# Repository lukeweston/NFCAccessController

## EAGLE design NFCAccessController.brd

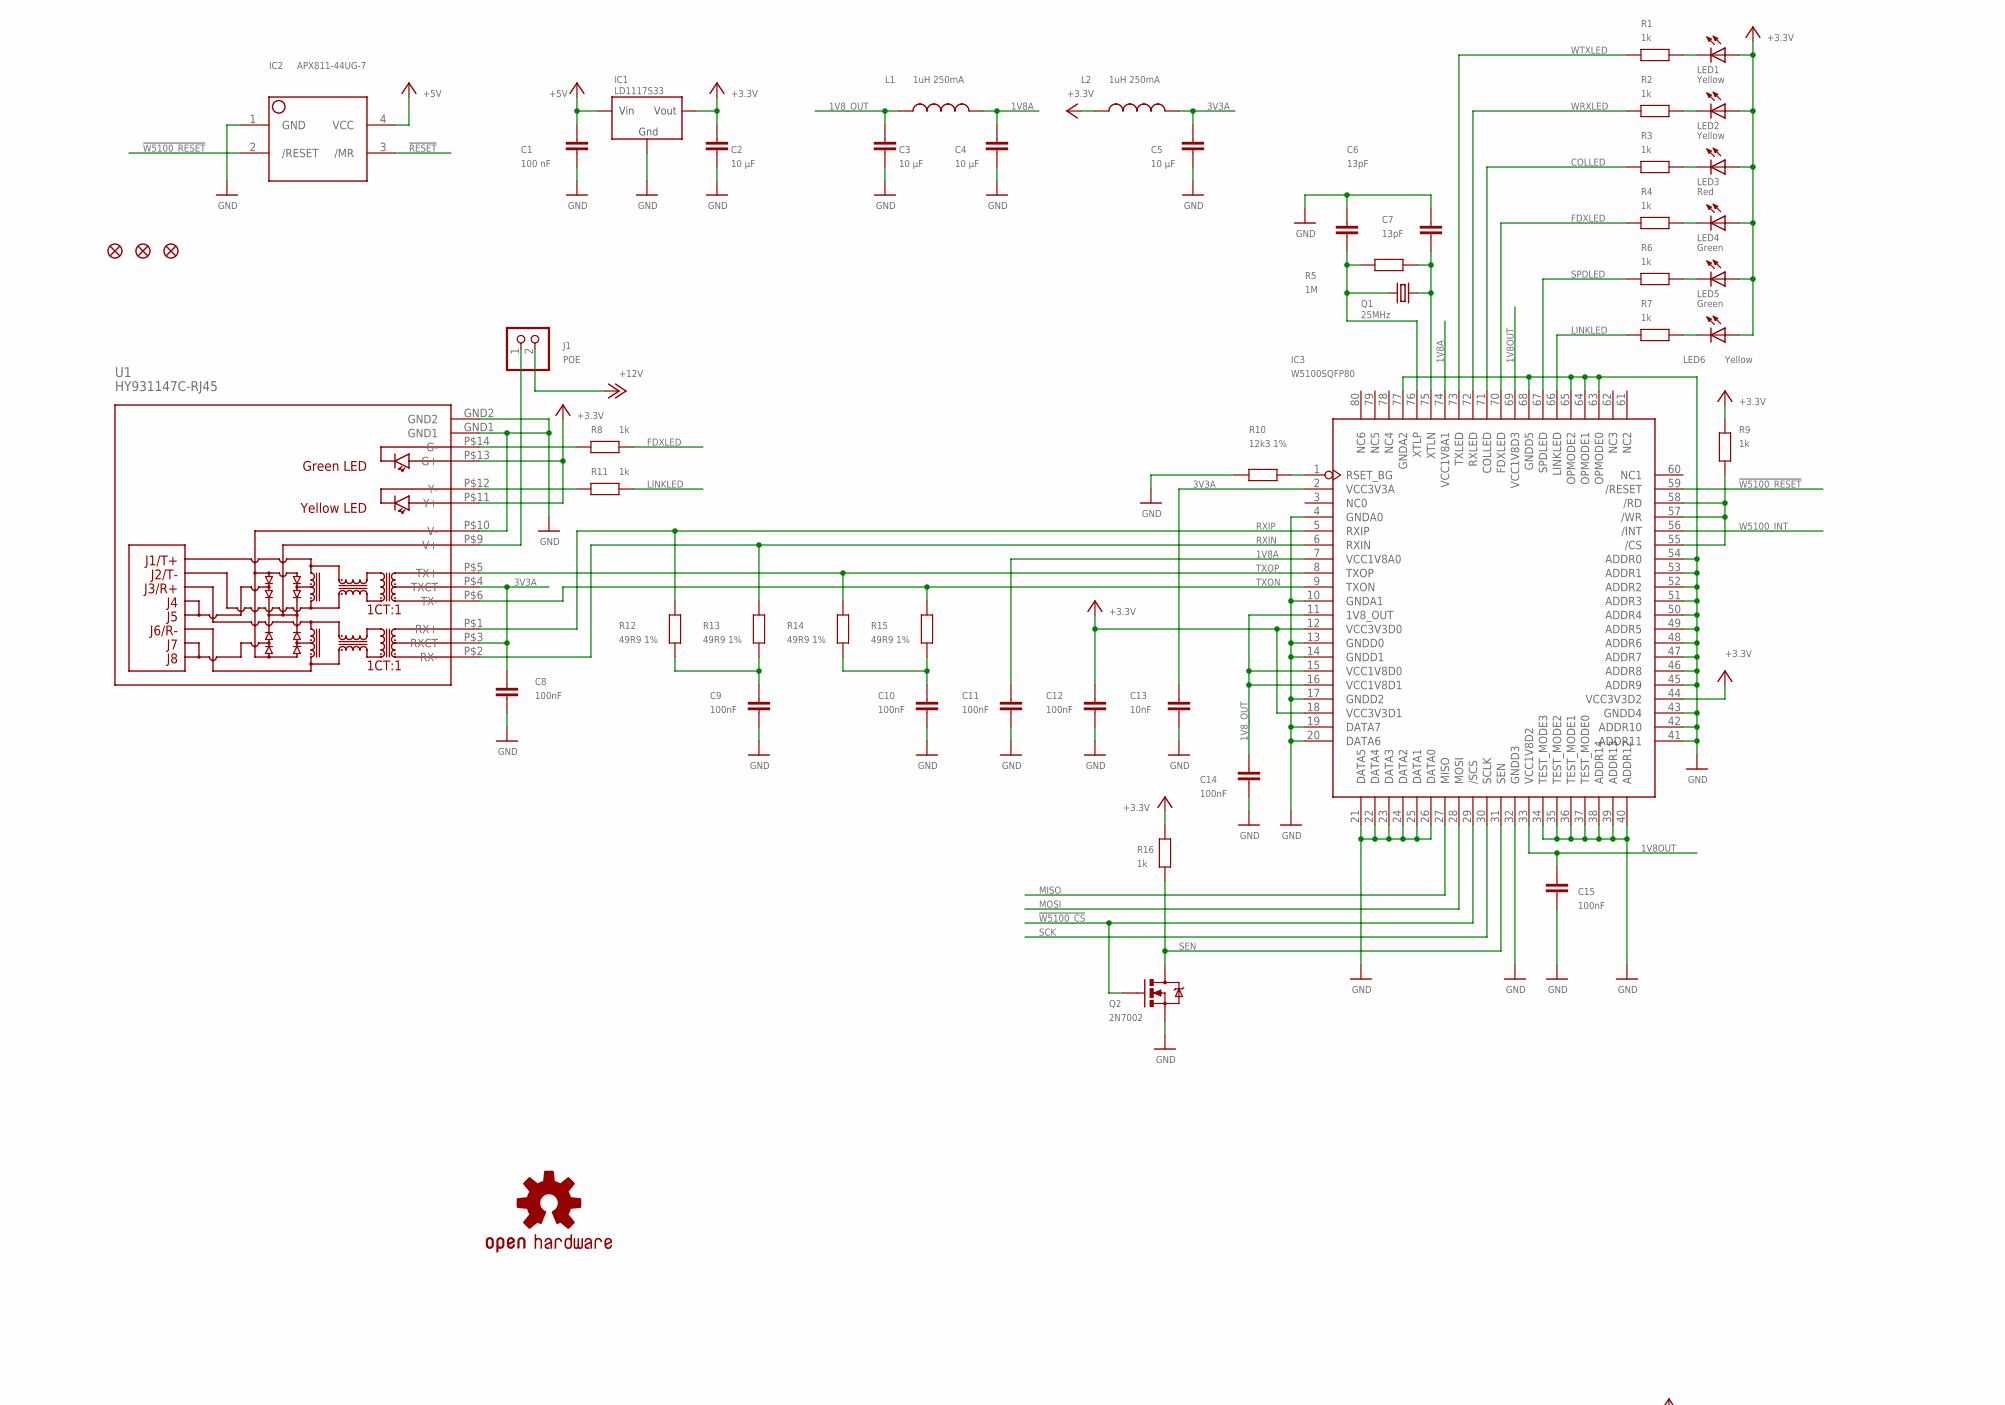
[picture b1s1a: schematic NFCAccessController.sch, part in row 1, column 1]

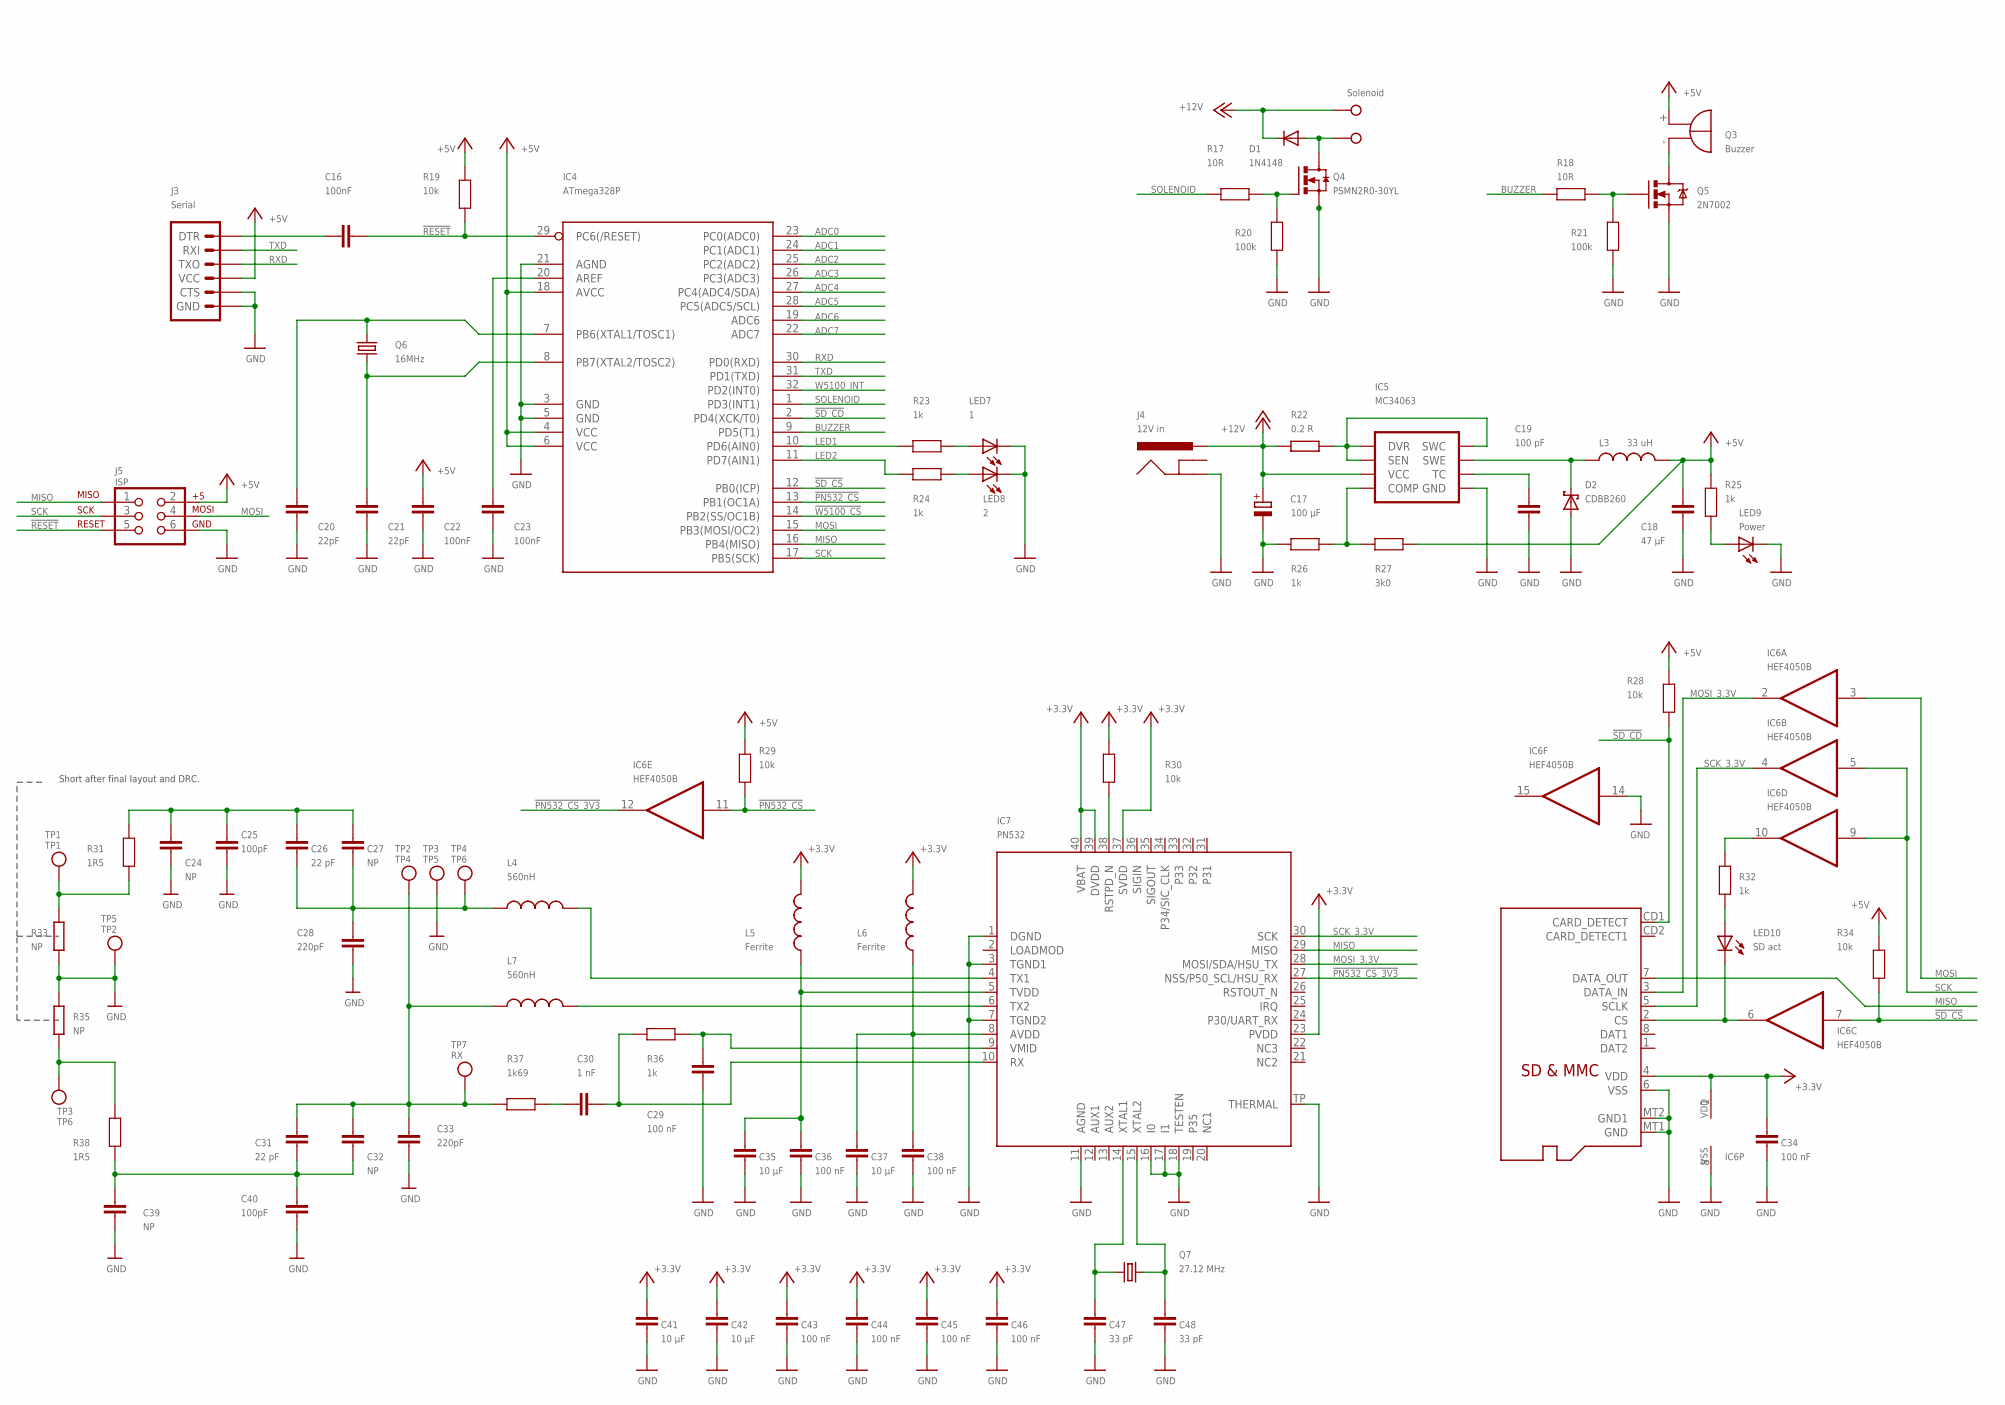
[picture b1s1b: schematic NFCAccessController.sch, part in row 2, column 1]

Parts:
C1, C29, C34, C36, C38, C43, C44, C45, C46: 100 nF; 0603
C2, C3, C4, C5, C35, C37, C41, C42: 10 µF; 0805
C6, C7: 13pF; 0603
C8, C9, C10, C11, C12, C14, C15, C16, C22, C23: 100nF; 0603
C13: 10nF; 0603
C17: 100 µF; E2,5-6
C18: 47 µF; C1210
C19: 100 pF; 0603
C20, C21: 22pF; 0603
C24, C27, C32, C39: NP; 0603
C25, C40: 100pF; 0603
C26, C31: 22 pF; 0603
C28, C33: 220pF; 0603
C30: 1 nF; 0603
C47, C48: 33 pF; 0603
D1: 1N4148; SOD-323
D2: CDBB260; SMB
FID1, FID2, FID3: FIDUCIAL1X2.5; FIDUCIAL-1X2.5
IC1: LD1117S33; SOT223; MPN REG1117
IC2: APX811-44UG-7; SOT143-R
IC3: W5100SQFP80; SQFP80
IC4: ATmega328P; TQFP32-08
IC5: MC34063; SO08
IC6: HEF4050B; SO16
IC7: PN532; HVQFN40-6X6
J1: POE; 1X02
J2: Solenoid; W237-132
J3: Serial; 1X06_LONGPADS
J4: 12V in; POWER_JACK_SLOT
J5: ISP; 2X3-NS
J6: MicroSD Card; ADAFRUIT_MICROSD
L1, L2: 1uH 250mA; L2012C
L3: 33 uH; CR75
L4, L7: 560nH; 0603
L5, L6: Ferrite; 0805-LARGE
LED1, LED2, LED6: Yellow; LED-0603
LED3: Red; LED-0603
LED4, LED5: Green; LED-0603
LED7: 1; LED-0603
LED8: 2; LED-0603
LED9: Power; LED-0603
LED10: SD act; LED-0603
Q1: 25MHz; HC49U-V
Q2, Q5: 2N7002; SOT23-3
Q3: Buzzer; F/TMB
Q4: PSMN2R0-30YL; SOT669
Q6: 16MHz; HC49U-V
Q7: 27.12 MHz; CRYSTAL-SMD-5X3
R1, R2, R3, R4, R6, R7, R8, R9, R11, R16, R23, R24, R25, R26, R32, R36: 1k; 0603
R5: 1M; 0603
R10: 12k3 1%; 0603
R12, R13, R14, R15: 49R9 1%; 0603
R17, R18: 10R; 0603
R19, R28, R29, R30, R34: 10k; 0603
R20, R21: 100k; 0603
R22: 0.2 R; R1210
R27: 3k0; 0603
R31, R38: 1R5; 0603
R33, R35: NP; R0201
R37: 1k69; 0603
S$1: OSHW-LOGOS; OSHW-LOGO-S
TP1: TP1; TESTPOINT_PAD_2MM
TP2: TP4; TESTPOINT_PAD_2MM
TP3: TP5; TESTPOINT_PAD_2MM
TP4: TP6; TESTPOINT_PAD_2MM
TP5: TP2; TESTPOINT_PAD_2MM
TP6: TP3; TESTPOINT_PAD_2MM
TP7: RX; TESTPOINT_PAD_2MM
U1: HY931147C-RJ45; HY931147C

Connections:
1V8A: C4.1, C11.1, IC3.7 (VCC1V8A0), IC3.74 (VCC1V8A1), L1.2
1V8OUT: C15.1, IC3.33 (VCC1V8D2), IC3.69 (VCC1V8D3)
1V8_OUT: C3.1, C14.1, IC3.11 (1V8_OUT), IC3.15 (VCC1V8D0), IC3.16 (VCC1V8D1), L1.1
3V3A: C5.1, C8.1, C13.1, IC3.2 (VCC3V3A), L2.2, U1.P$3 (RXCT), U1.P$4 (TXCT)
!PN532_CS: IC4.13 (PB1(OC1A)), IC6.11 (I), R29.2
!PN532_CS_3V3: IC6.12 (O), IC7.27 (NSS/P50_SCL/HSU_RX)
!RESET: C16.2, IC2.3 (/MR), IC4.29 (PC6(/RESET)), J5.5, R19.1
!SD_CD: IC4.2 (PD4(XCK/T0)), J6.CD1 (CARD_DETECT), R28.1
!SD_CS: IC4.12 (PB0(ICP)), IC6.7 (I), R34.1
!W5100_CS: IC3.29 (/SCS), IC4.14 (PB2(SS/OC1B)), Q2.1 (G)
!W5100_RESET: IC2.2 (/RESET), IC3.59 (/RESET)
+3V3: C2.1, C12.1, C34.1, C41.1, C42.1, C43.1, C44.1, C45.1, C46.1, IC1.2 (VOUT), IC3.12 (VCC3V3D0), IC3.18 (VCC3V3D1), IC3.44 (VCC3V3D2), IC6.1 (VDD), IC7.23 (PVDD), IC7.37 (SVDD), IC7.39 (DVDD), IC7.40 (VBAT), J6.4 (VDD), L2.1, L5.2, L6.2, LED1.A, LED2.A, LED3.A, LED4.A, LED5.A, LED6.A, R9.1, R16.1, R30.1, U1.P$11 (Y+), U1.P$13 (G+)
+5V: C1.1, C18.1, C22.1, IC1.3 (VIN), IC2.4 (VCC), IC4.4 (VCC), IC4.6 (VCC), IC4.18 (AVCC), J3.4 (VCC), J5.2, L3.P$2 (2), Q3.+, R19.2, R25.2, R27.1, R28.2, R29.1, R34.2
+12V: C17.+, D1.1 (C), IC5.6 (VCC), J1.2, J2.1, J4.PWR, R22.1
ADC0: IC4.23 (PC0(ADC0))
ADC1: IC4.24 (PC1(ADC1))
ADC2: IC4.25 (PC2(ADC2))
ADC3: IC4.26 (PC3(ADC3))
ADC4: IC4.27 (PC4(ADC4/SDA))
ADC5: IC4.28 (PC5(ADC5/SCL))
ADC6: IC4.19 (ADC6)
ADC7: IC4.22 (ADC7)
AREF: C23.1, IC4.20 (AREF)
BUZZER: IC4.9 (PD5(T1)), R18.1
COLLED: IC3.71 (COLLED), R3.1
FDXLED: IC3.70 (FDXLED), R4.1, R8.2
FOO: IC6.6 (O), J6.2 (CS), LED10.C
GND: C1.2, C2.2, C3.2, C4.2, C5.2, C6.1, C7.1, C8.2, C9.2, C10.2, C11.2, C12.2, C13.2, C14.2, C15.2, C17.-, C18.2, C19.2, C20.2, C21.2, C22.2, C23.2, C24.1, C25.1, C28.1, C29.2, C33.2, C34.2, C35.2, C36.2, C37.2, C38.2, C39.2, C40.2, C41.2, C42.2, C43.2, C44.2, C45.2, C46.2, C47.2, C48.2, D2.A, IC1.1 (GND), IC2.1 (GND), IC3.4 (GNDA0), IC3.10 (GNDA1), IC3.13 (GNDD0), IC3.14 (GNDD1), IC3.17 (GNDD2), IC3.19 (DATA7), IC3.20 (DATA6), IC3.21 (DATA5), IC3.22 (DATA4), IC3.23 (DATA3), IC3.24 (DATA2), IC3.25 (DATA1), IC3.26 (DATA0), IC3.32 (GNDD3), IC3.34 (TEST_MODE3), IC3.35 (TEST_MODE2), IC3.36 (TEST_MODE1), IC3.37 (TEST_MODE0), IC3.38 (ADDR14), IC3.39 (ADDR13), IC3.40 (ADDR12), IC3.41 (ADDR11), IC3.42 (ADDR10), IC3.43 (GNDD4), IC3.45 (ADDR9), IC3.46 (ADDR8), IC3.47 (ADDR7), IC3.48 (ADDR6), IC3.49 (ADDR5), IC3.50 (ADDR4), IC3.51 (ADDR3), IC3.52 (ADDR2), IC3.53 (ADDR1), IC3.54 (ADDR0), IC3.63 (OPMODE0), IC3.64 (OPMODE1), IC3.65 (OPMODE2), IC3.68 (GNDD5), IC3.77 (GNDA2), IC4.3 (GND), IC4.5 (GND), IC4.21 (AGND), IC5.4 (GND), IC6.8 (VSS), IC6.14 (I), IC7.1 (DGND), IC7.3 (TGND1), IC7.7 (TGND2), IC7.11 (AGND), IC7.16 (I0), IC7.17 (I1), IC7.18 (TESTEN), IC7.TP (THERMAL), J3.5 (CTS), J3.6 (GND), J4.GND, J5.6, J6.6 (VSS), J6.MT1 (GND), J6.MT2 (GND1), LED7.C, LED8.C, LED9.C, Q2.2 (S), Q4.1 (S), Q4.2 (S), Q4.3 (S), Q5.2 (S), R10.1, R20.2, R21.1, R26.2, R33.1, R35.2, TP3.P$1, TP5.P$1, U1.GND1, U1.GND2, U1.P$10 (V-)
LED1: IC4.10 (PD6(AIN0)), R23.1
LED2: IC4.11 (PD7(AIN1)), R24.1
LINKLED: IC3.66 (LINKLED), R7.1, R11.2
MISO: IC3.27 (MISO), IC4.16 (PB4(MISO)), IC7.29 (MISO), J5.1, J6.7 (DATA_OUT)
MOSI: IC3.28 (MOSI), IC4.15 (PB3(MOSI/OC2)), IC6.3 (I), J5.4
MOSI_3.3V: IC6.2 (O), IC7.28 (MOSI/SDA/HSU_TX), J6.3 (DATA_IN)
unnamed: IC7.4 (TX1), L4.2
unnamed: IC7.6 (TX2), L7.2
unnamed: C26.1, C27.1, C28.2, L4.1, TP4.P$1
unnamed: R31.1, R33.2, TP1.P$1
unnamed: R35.1, R38.2, TP6.P$1
unnamed: IC5.1 (SWC), IC5.7 (SEN), IC5.8 (DVR), R22.2
unnamed: C47.1, IC7.14 (XTAL1), Q7.1
unnamed: C48.1, IC7.15 (XTAL2), Q7.3 (2)
unnamed: C30.1, R37.2
unnamed: C29.1, IC7.9 (VMID), R36.2
unnamed: C30.2, IC7.10 (RX), R36.1
unnamed: C31.2, C32.2, C33.1, L7.1, R37.1, TP2.P$1, TP7.P$1
unnamed: C37.1, C38.1, IC7.8 (AVDD), L6.1
unnamed: C7.2, IC3.75 (XTLN), Q1.1, R5.2
unnamed: C35.1, C36.1, IC7.5 (TVDD), L5.1
unnamed: C19.1, IC5.3 (TC)
unnamed: IC5.5 (COMP), R26.1, R27.2
unnamed: LED9.A, R25.1
unnamed: C6.2, IC3.76 (XTLP), Q1.2, R5.1
unnamed: C9.1, R12.1, R13.1
unnamed: D2.C, IC5.2 (SWE), L3.P$1 (1)
unnamed: Q4.4 (G), R17.2, R20.1
unnamed: Q5.1 (G), R18.2, R21.2
unnamed: C10.1, R14.1, R15.1
unnamed: D1.2 (A), J2.2, Q4.MB (D)
unnamed: Q3.-, Q5.3 (D)
unnamed: LED7.A, R23.2
unnamed: LED8.A, R24.2
unnamed: C20.1, IC4.7 (PB6(XTAL1/TOSC1)), Q6.2
unnamed: C21.1, IC4.8 (PB7(XTAL2/TOSC2)), Q6.1
unnamed: IC3.55 (/CS), IC3.57 (/WR), IC3.58 (/RD), R9.2
unnamed: LED5.C, R6.2
unnamed: LED6.C, R7.2
unnamed: C16.1, J3.1 (DTR)
unnamed: LED10.A, R32.1
unnamed: IC6.10 (O), R32.2
unnamed: R8.1, U1.P$14 (G-)
unnamed: J1.1, U1.P$9 (V+)
unnamed: IC3.1 (RSET_BG), R10.2
unnamed: LED4.C, R4.2
unnamed: LED3.C, R3.2
unnamed: LED2.C, R2.2
unnamed: LED1.C, R1.2
unnamed: R11.1, U1.P$12 (Y-)
RSTPD_N: IC7.38 (RSTPD_N), R30.2
RXD: IC4.30 (PD0(RXD)), J3.3 (TXO)
RXIN: IC3.6 (RXIN), R13.2, U1.P$2 (RX-)
RXIP: IC3.5 (RXIP), R12.2, U1.P$1 (RX+)
SCK: IC3.30 (SCLK), IC4.17 (PB5(SCK)), IC6.5 (I), IC6.9 (I), J5.3
SCK_3.3V: IC6.4 (O), IC7.30 (SCK), J6.5 (SCLK)
SEN: IC3.31 (SEN), Q2.3 (D), R16.2
SOLENOID: IC4.1 (PD3(INT1)), R17.1
SPDLED: IC3.67 (SPDLED), R6.1
TX1_ANTENNA: C24.2, C25.2, C26.2, C27.2, R31.2
TX2_ANTENNA: C31.1, C32.1, C39.1, C40.1, R38.1
TXD: IC4.31 (PD1(TXD)), J3.2 (RXI)
TXON: IC3.9 (TXON), R15.2, U1.P$6 (TX-)
TXOP: IC3.8 (TXOP), R14.2, U1.P$5 (TX+)
W5100_INT: IC3.56 (/INT), IC4.32 (PD2(INT0))
WRXLED: IC3.72 (RXLED), R2.1
WTXLED: IC3.73 (TXLED), R1.1

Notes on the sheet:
Short after final layout and DRC.

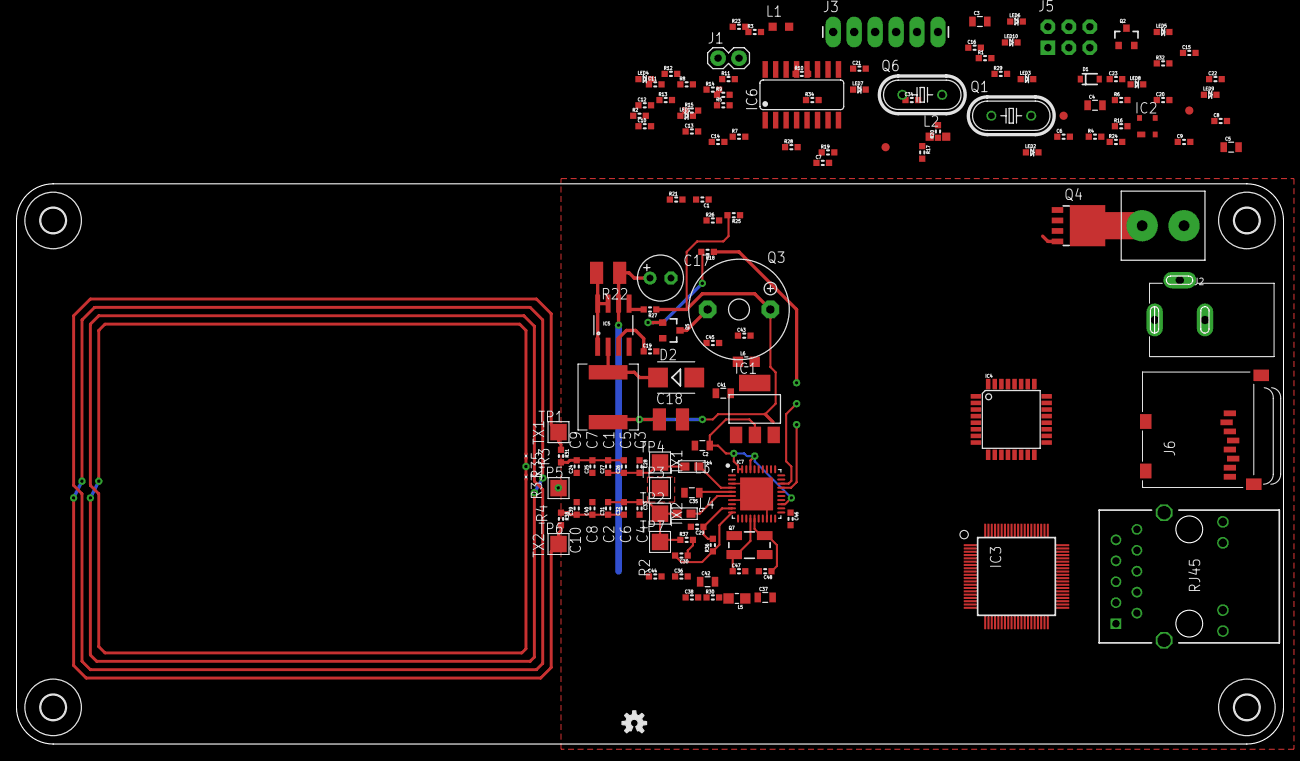
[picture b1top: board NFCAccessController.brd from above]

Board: 2 copper layers, 153.7 x 67.9 mm, 141 parts (0 on the bottom side), 87 nets.

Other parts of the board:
U$6, U$36, U$37, U$38: MOUNTINGHOLE_3.0

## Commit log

2012-09-14 added readme

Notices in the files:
NFCAccessController.sch:
Released under the CERN Open Hardware License:
